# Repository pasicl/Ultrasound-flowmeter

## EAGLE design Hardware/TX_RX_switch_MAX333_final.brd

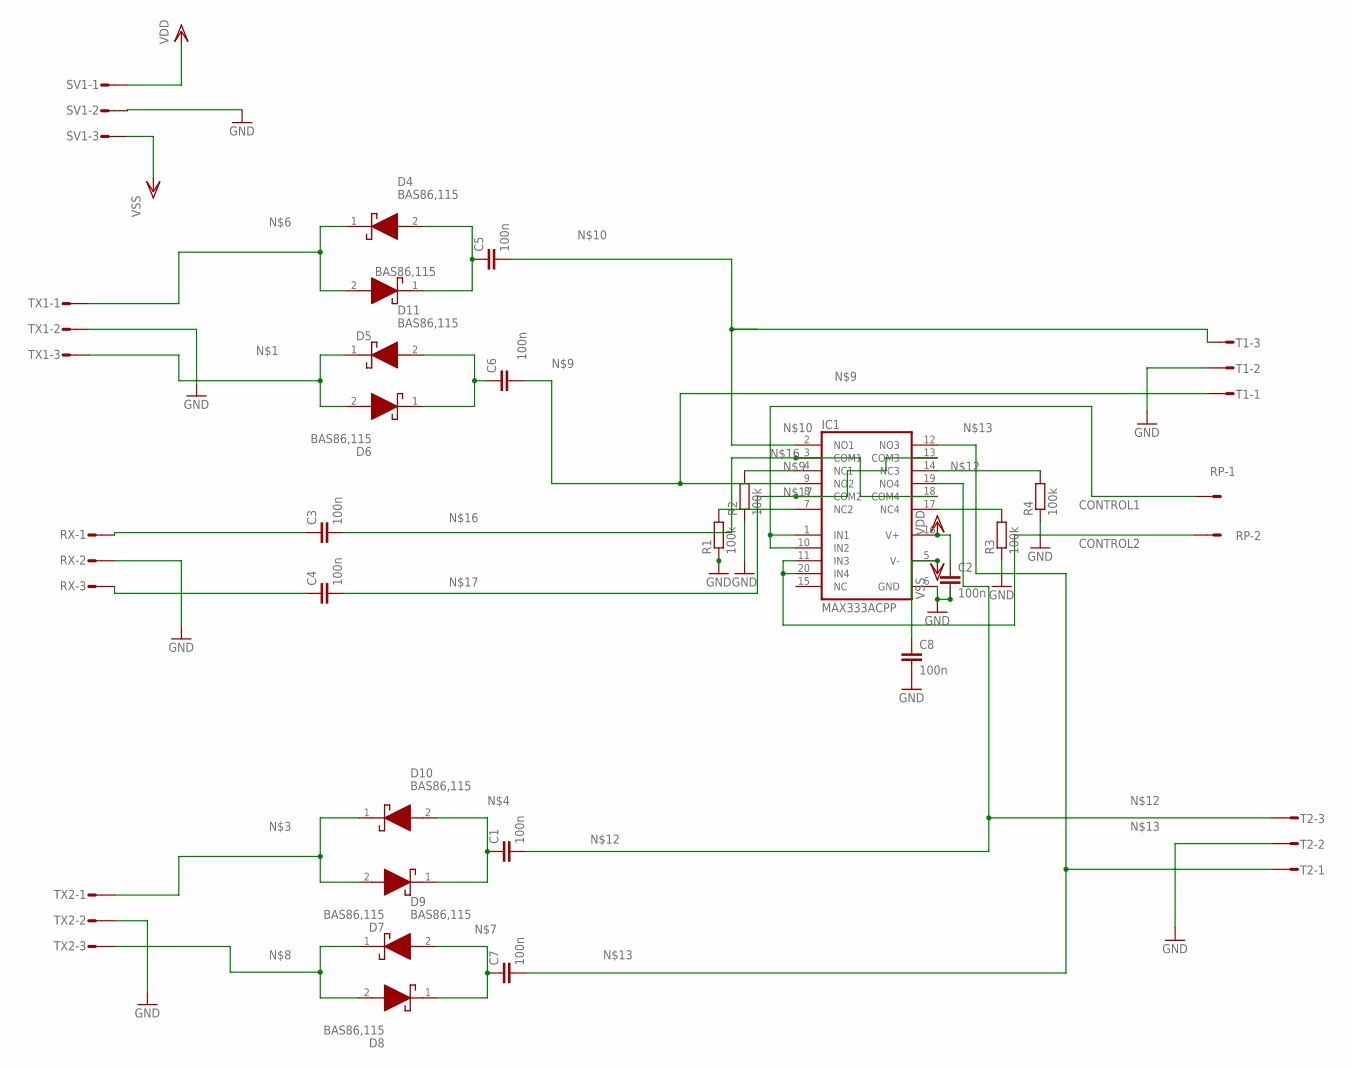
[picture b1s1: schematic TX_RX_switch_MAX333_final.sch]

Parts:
C1, C2, C3, C4, C5, C6, C7, C8: 100n; C1206
D4, D5, D6, D7, D8, D9, D10, D11: BAS86,115; BAS86115
IC1: MAX333ACPP; DIL20
R1, R2, R3, R4: 100k; R1206
RP: L02P
RX: L03P
SV1: L03P
T1, T2: L03P
TX1, TX2: L03P

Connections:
CONTROL1: IC1.1 (IN1), IC1.10 (IN2), RP.1
CONTROL2: IC1.11 (IN3), IC1.20 (IN4), RP.2
GND: C2.2, C8.2, IC1.6 (GND), R1.1, R2.1, R3.1, R4.1
GND3: RX.2, SV1.2, T1.2, T2.2, TX1.2, TX2.2
unnamed: D6.2 (A), D11.1 (K), TX1.3
unnamed: C6.1, D6.1 (K), D11.2 (A)
unnamed: D7.2 (A), D10.1 (K), TX2.1
unnamed: C1.1, D7.1 (K), D10.2 (A)
unnamed: C5.1, D4.2 (A), D5.1 (K)
unnamed: D4.1 (K), D5.2 (A), TX1.1
unnamed: C7.1, D8.1 (K), D9.2 (A)
unnamed: D8.2 (A), D9.1 (K), TX2.3
unnamed: C6.2, IC1.9 (NO2), T1.1
unnamed: C5.2, IC1.2 (NO1), T1.3
unnamed: C1.2, IC1.19 (NO4), T2.3
unnamed: C7.2, IC1.12 (NO3), T2.1
unnamed: IC1.7 (NC2), R1.2
unnamed: C4.1, RX.3
unnamed: C3.2, IC1.3 (COM1), IC1.18 (COM4)
unnamed: C4.2, IC1.8 (COM2), IC1.13 (COM3)
unnamed: C3.1, RX.1
unnamed: IC1.4 (NC1), R2.2
unnamed: IC1.14 (NC3), R4.2
unnamed: IC1.17 (NC4), R3.2
VDD: C2.1, IC1.16 (V+), SV1.1
VSS: C8.1, IC1.5 (V-), SV1.3

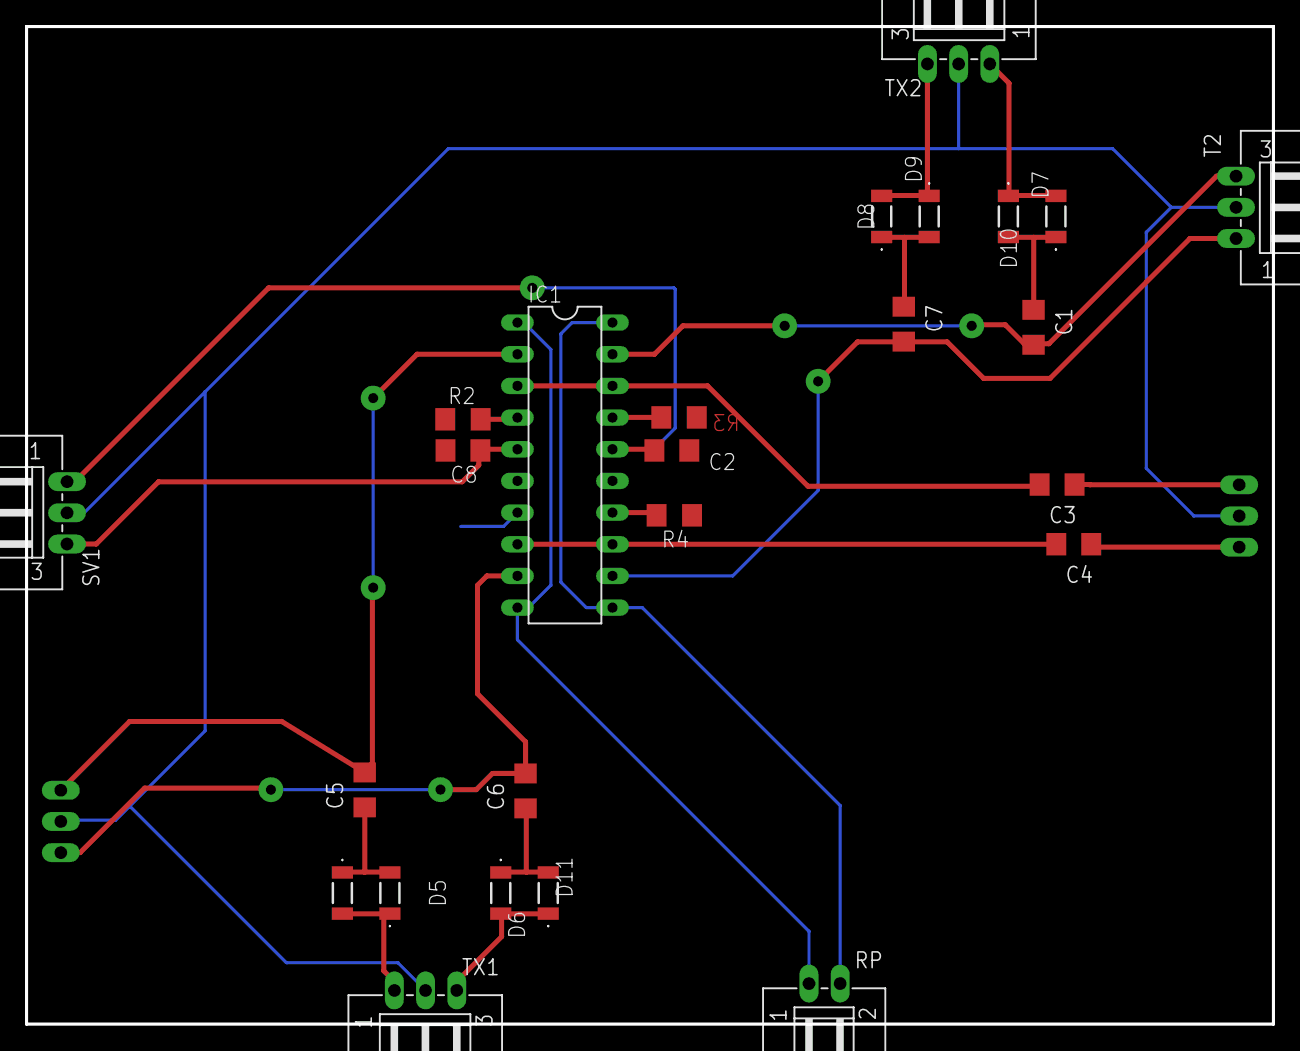
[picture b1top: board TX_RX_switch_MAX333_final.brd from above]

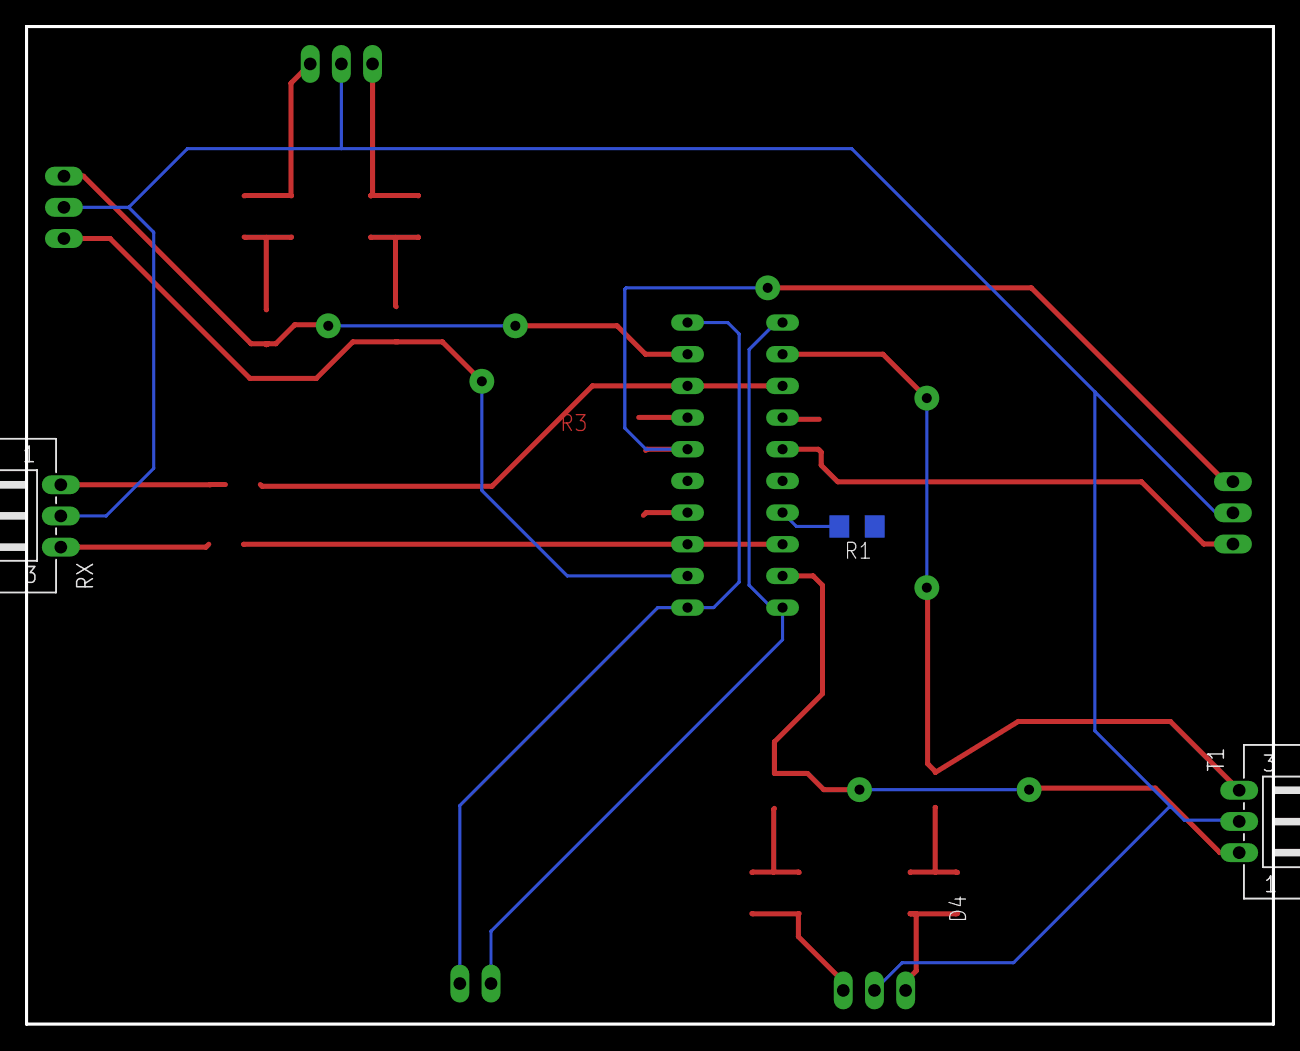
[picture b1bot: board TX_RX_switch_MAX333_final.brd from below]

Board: 2 copper layers, 100.0 x 80.0 mm, 28 parts (3 on the bottom side), 26 nets.
